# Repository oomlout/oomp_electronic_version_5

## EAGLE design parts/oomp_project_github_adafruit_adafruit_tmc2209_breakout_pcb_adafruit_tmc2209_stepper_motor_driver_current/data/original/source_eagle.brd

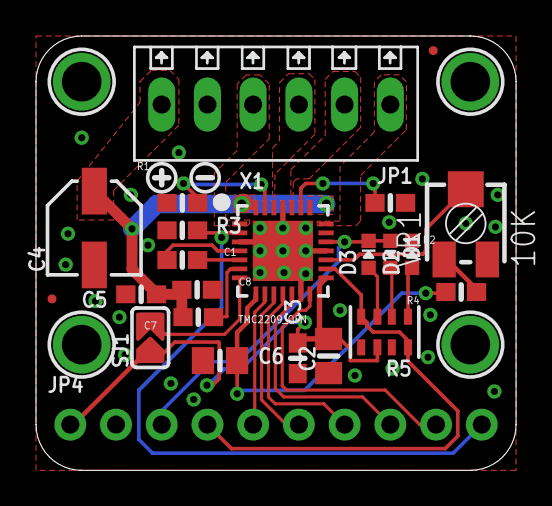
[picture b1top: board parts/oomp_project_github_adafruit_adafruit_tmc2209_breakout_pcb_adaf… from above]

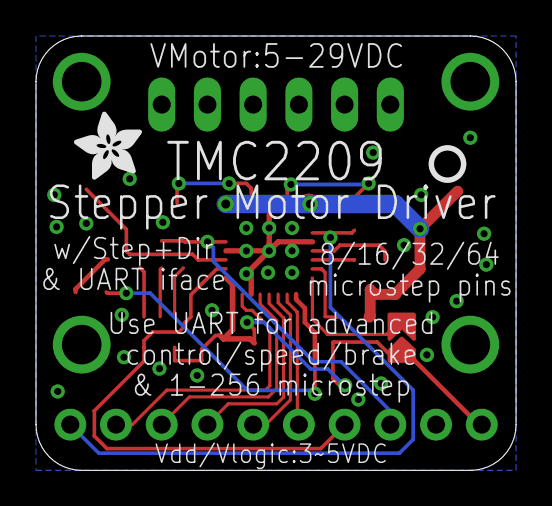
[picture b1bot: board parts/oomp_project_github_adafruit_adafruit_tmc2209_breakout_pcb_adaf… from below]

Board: 2 copper layers, 26.7 x 24.1 mm, 52 parts (2 on the bottom side), 27 nets.

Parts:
C1: 22nF/50V; 0603-NO
C2, C6: 10uF; 0805-NO
C3, C5, C7, C8: 0.22uF/50V; 0603-NO
C4: 22uF/50V; PANASONIC_C
D1: RED; CHIPLED_0603_NOOUTLINE
D2: YELLOW; CHIPLED_0603_NOOUTLINE
D3: GREEN; CHIPLED_0603_NOOUTLINE
JP1: 6-pin 2.54 Terminal; 1X06_2.54MMTERMINAL
JP4: 1X10_ROUND70
PLABEL0: PLABEL0
PLABEL1: PLABEL1
PLABEL2: PLABEL2
PLABEL3: PLABEL3
PLABEL4: PLABEL4
PLABEL5: PLABEL5
PLABEL6: PLABEL6
PLABEL7: PLABEL7
PLABEL8: PLABEL8
PLABEL9: PLABEL9
PLABEL10: PLABEL10
PLABEL11: PLABEL11
PLABEL12: PLABEL12
PLABEL13: PLABEL13
PLABEL14: PLABEL14
PLABEL15: PLABEL15
PLABEL16: PLABEL16
PLABEL17: PLABEL17
PLABEL18: PLABEL18
PLABEL19: PLABEL19
PLABEL20: PLABEL20
R1, R2: 0.05Ω/0.25W; 0603-NO
R3: 20K; 0603-NO
R4: 33K; 0603-NO
R5: 20K Pack; RESPACK_4X0603
SJ1: SOLDERJUMPER_ARROW_NOPASTE
U$7: SYMBOL_PLUS
U$8: SYMBOL_MINUS
U$10, U$11: FIDUCIAL_0.5MM
U$12: PCBFEAT-REV-040
U$18, U$22, U$26, U$27: MOUNTINGHOLE2.0; MOUNTINGHOLE_2.0_PLATED
U$24: ADAFRUIT_3.5MM
VR1: 10K; RTRIM3314J
X1: TMC2209_QFN; QFN28_5MM_MICROCHIP

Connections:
+5V: C6.2, R4.2, X1.8
BRA: R2.2, X1.23
BRB: R1.2, X1.27
DIAG: JP4.7, X1.11
DIR: D1.A, D3.C, JP4.3, X1.19
ENABLE: JP4.10, R3.2, X1.2
GND: C2.1, C3.1, C4.-, C5.2, C6.1, C8.2, D2.C, JP1.5, JP4.2, R1.1, R2.1, R3.1, R5.5, R5.7, VR1.1, X1.3, X1.13, X1.18, X1.25, X1.THERMAL
INDEX: JP4.8, X1.12
MS1: JP4.5, X1.9
MS2: JP4.6, X1.10
unnamed: D2.A, R5.1
unnamed: C1.1, X1.4
unnamed: C1.2, X1.5
unnamed: R4.1, VR1.3
unnamed: C7.1, X1.6
unnamed: D1.C, R5.2
unnamed: D3.A, R5.3
OUT1A: JP1.2, X1.24
OUT1B: JP1.1, X1.21
OUT2A: JP1.3, X1.26
OUT2B: JP1.4, X1.1
SPREAD: SJ1.2, X1.7
STEP: JP4.4, R5.4, R5.8, X1.16
UART: JP4.9, X1.14
VDD: C2.2, C3.2, JP4.1, R5.6, SJ1.1, X1.15
VMOTOR: C4.+, C5.1, C7.2, C8.1, JP1.6, X1.22, X1.28
VREF: VR1.2, X1.17

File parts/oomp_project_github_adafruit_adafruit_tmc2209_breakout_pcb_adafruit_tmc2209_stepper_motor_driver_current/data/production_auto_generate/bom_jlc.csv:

Comment,Designator,Footprint,LCSC Part #
,JP4,Adafruit TMC2209 Stepper Motor Driver-import-fps:1X10_ROUND70,C57369
,U$24,Adafruit TMC2209 Stepper Motor Driver-import-fps:ADAFRUIT_3.5MM,
,U$12,Adafruit TMC2209 Stepper Motor Driver-import-fps:PCBFEAT-REV-040,
,PLABEL0,Adafruit TMC2209 Stepper Motor Driver-import-fps:PLABEL0,
,PLABEL1,Adafruit TMC2209 Stepper Motor Driver-import-fps:PLABEL1,
,PLABEL10,Adafruit TMC2209 Stepper Motor Driver-import-fps:PLABEL10,
,PLABEL11,Adafruit TMC2209 Stepper Motor Driver-import-fps:PLABEL11,
,PLABEL12,Adafruit TMC2209 Stepper Motor Driver-import-fps:PLABEL12,
,PLABEL13,Adafruit TMC2209 Stepper Motor Driver-import-fps:PLABEL13,
,PLABEL14,Adafruit TMC2209 Stepper Motor Driver-import-fps:PLABEL14,
,PLABEL15,Adafruit TMC2209 Stepper Motor Driver-import-fps:PLABEL15,
,PLABEL16,Adafruit TMC2209 Stepper Motor Driver-import-fps:PLABEL16,
,PLABEL17,Adafruit TMC2209 Stepper Motor Driver-import-fps:PLABEL17,
,PLABEL18,Adafruit TMC2209 Stepper Motor Driver-import-fps:PLABEL18,
,PLABEL19,Adafruit TMC2209 Stepper Motor Driver-import-fps:PLABEL19,
,PLABEL2,Adafruit TMC2209 Stepper Motor Driver-import-fps:PLABEL2,
,PLABEL20,Adafruit TMC2209 Stepper Motor Driver-import-fps:PLABEL20,
,PLABEL3,Adafruit TMC2209 Stepper Motor Driver-import-fps:PLABEL3,
,PLABEL4,Adafruit TMC2209 Stepper Motor Driver-import-fps:PLABEL4,
,PLABEL5,Adafruit TMC2209 Stepper Motor Driver-import-fps:PLABEL5,
,PLABEL6,Adafruit TMC2209 Stepper Motor Driver-import-fps:PLABEL6,
,PLABEL7,Adafruit TMC2209 Stepper Motor Driver-import-fps:PLABEL7,
,PLABEL8,Adafruit TMC2209 Stepper Motor Driver-import-fps:PLABEL8,
,PLABEL9,Adafruit TMC2209 Stepper Motor Driver-import-fps:PLABEL9,
,U$8,Adafruit TMC2209 Stepper Motor Driver-import-fps:SYMBOL_MINUS,
,U$7,Adafruit TMC2209 Stepper Motor Driver-import-fps:SYMBOL_PLUS,
0.05Ω/0.25W,"R1,R2",Adafruit TMC2209 Stepper Motor Driver-import-fps:0603-NO,
0.22uF/50V,"C3,C5,C7,C8",Adafruit TMC2209 Stepper Motor Driver-import-fps:0603-NO,
10K,VR1,Adafruit TMC2209 Stepper Motor Driver-import-fps:RTRIM3314J,
10uF,"C2,C6",Adafruit TMC2209 Stepper Motor Driver-import-fps:0805-NO,
20K,R3,Adafruit TMC2209 Stepper Motor Driver-import-fps:0603-NO,
20K Pack,R5,Adafruit TMC2209 Stepper Motor Driver-import-fps:RESPACK_4X0603,
22nF/50V,C1,Adafruit TMC2209 Stepper Motor Driver-import-fps:0603-NO,
22uF/50V,C4,Adafruit TMC2209 Stepper Motor Driver-import-fps:PANASONIC_C,
33K,R4,Adafruit TMC2209 Stepper Motor Driver-import-fps:0603-NO,C4216
6-pin 2.54 Terminal,JP1,Adafruit TMC2209 Stepper Motor Driver-import-fps:1X06_2.54MMTERMINAL,C37208
FIDUCIAL_0.5MM,"U$10,U$11",Adafruit TMC2209 Stepper Motor Driver-import-fps:FIDUCIAL_0.5MM,
GREEN,D3,Adafruit TMC2209 Stepper Motor Driver-import-fps:CHIPLED_0603_NOOUTLINE,
RED,D1,Adafruit TMC2209 Stepper Motor Driver-import-fps:CHIPLED_0603_NOOUTLINE,
TMC2209_QFN,X1,Adafruit TMC2209 Stepper Motor Driver-import-fps:QFN28_5MM_MICROCHIP,
YELLOW,D2,Adafruit TMC2209 Stepper Motor Driver-import-fps:CHIPLED_0603_NOOUTLINE,

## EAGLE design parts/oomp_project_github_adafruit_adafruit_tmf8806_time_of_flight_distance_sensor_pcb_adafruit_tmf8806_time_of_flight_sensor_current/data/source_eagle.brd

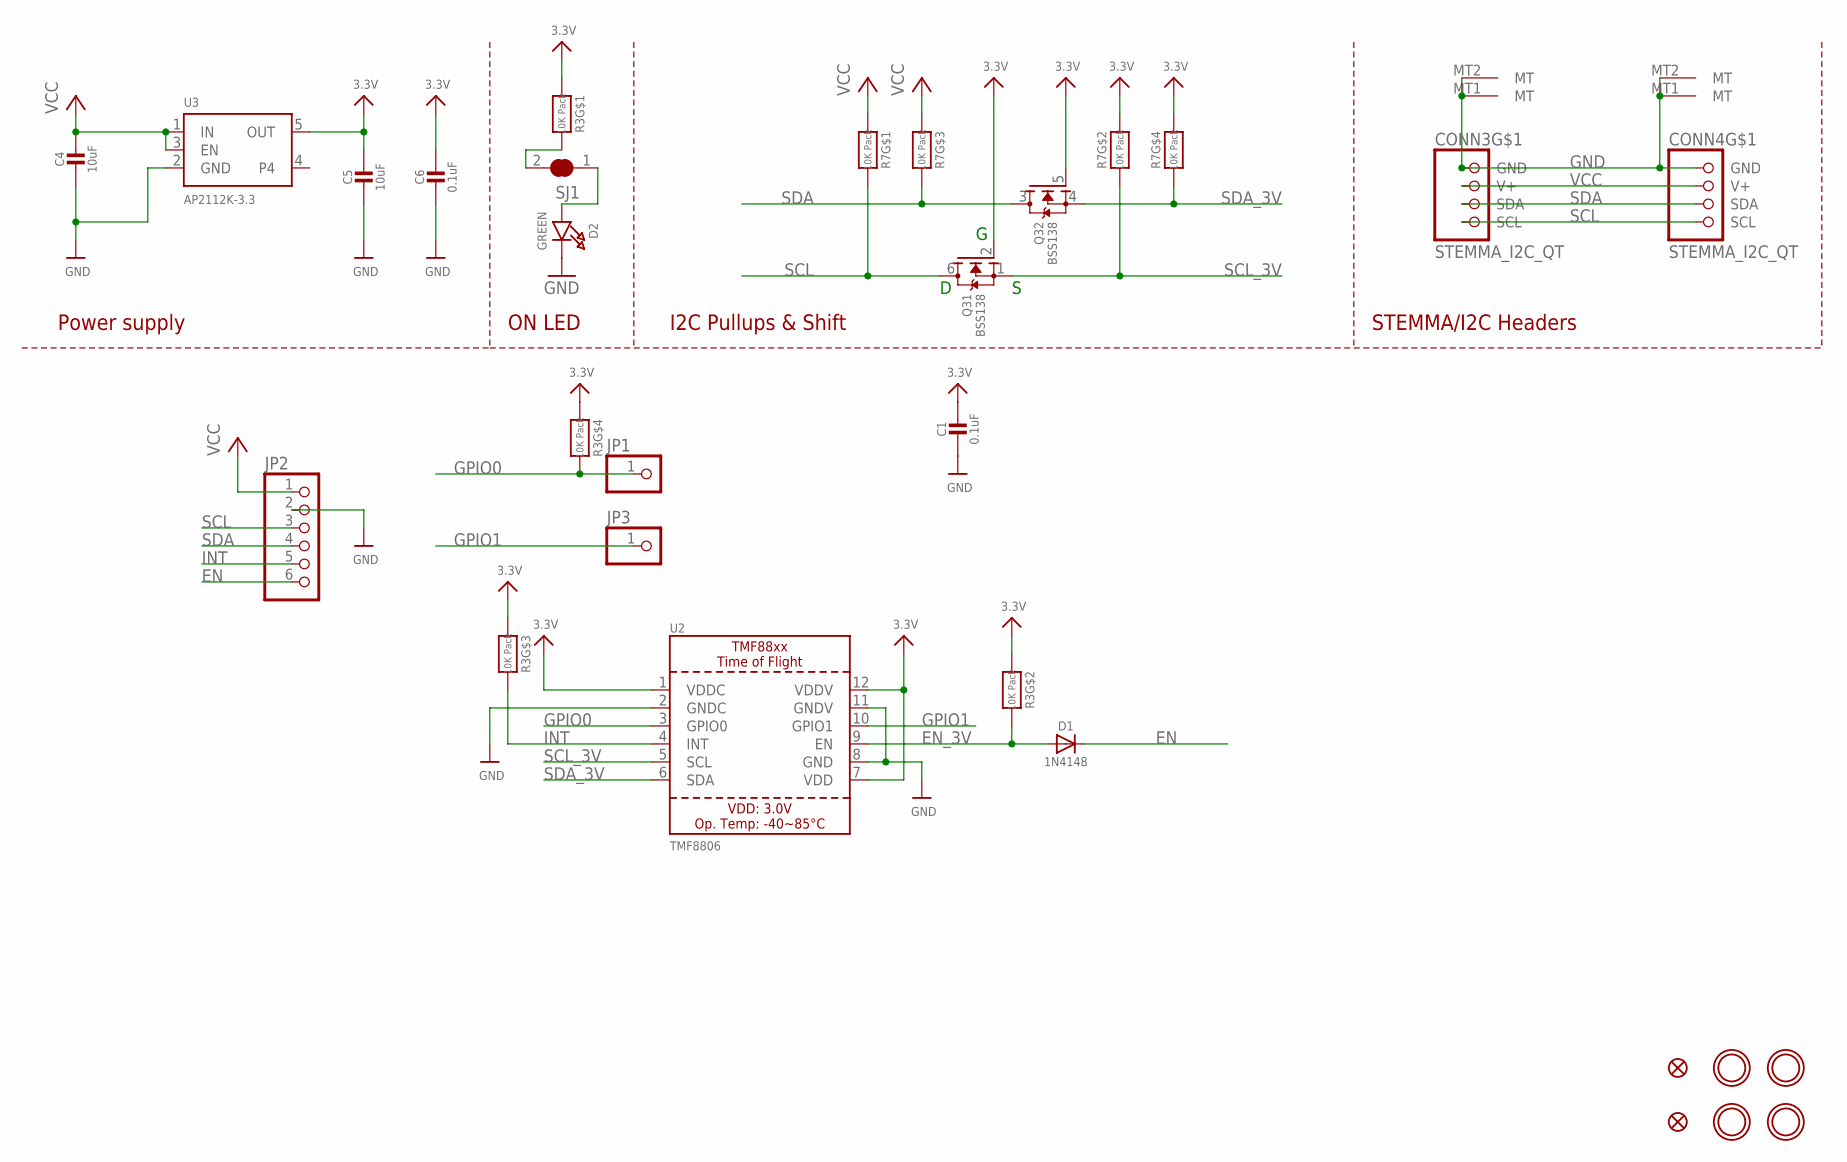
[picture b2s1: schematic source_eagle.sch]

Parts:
C1, C6: 0.1uF; 0603-NO
C4, C5: 10uF; 0805-NO
CONN3, CONN4: STEMMA_I2C_QT; JST_SH4
D1: 1N4148; SOD-323
D2: GREEN; CHIPLED_0603_NOOUTLINE
FID1, FID4: FIDUCIAL_0.5MM
JP1, JP3: HEADER-1X1ROUND; 1X01_ROUND
JP2: HEADER-1X670MIL; 1X06_ROUND_70
Q3: BSS138; SOT363
R3, R7: 10K Pack; RESPACK_4X0603
SJ1: SOLDERJUMPER_CLOSED; SOLDERJUMPER_CLOSEDWIRE
U2: TMF8806; TMF880X
U3: AP2112K-3.3; SOT23-5; JLC_ROTATION 0
U$30, U$31, U$33, U$34: MOUNTINGHOLE2.5; MOUNTINGHOLE_2.5_PLATED

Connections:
3.3V: C1.1, C5.1, C6.1, Q3.2 (G), Q3.5 (G), R3.1, R3.2 (1), R3.3 (1), R3.4 (1), R7.2 (1), R7.4 (1), U2.1 (VDDC), U2.7 (VDD), U2.12 (VDDV), U3.5 (OUT)
EN: D1.C, JP2.6
EN_3V: D1.A, R3.7 (2), U2.9 (EN)
GND: C1.2, C4.2, C5.2, C6.2, CONN3.1 (GND), CONN3.MT1 (MT), CONN3.MT2 (MT), CONN4.1 (GND), CONN4.MT1 (MT), CONN4.MT2 (MT), D2.C, JP2.2, U2.2 (GNDC), U2.8 (GND), U2.11 (GNDV), U3.2 (GND)
GPIO0: JP1.1, R3.5 (2), U2.3 (GPIO0)
GPIO1: JP3.1, U2.10 (GPIO1)
INT: JP2.5, R3.6 (2), U2.4 (INT)
unnamed: R3.8 (2), SJ1.2
unnamed: D2.A, SJ1.1
SCL: CONN3.4 (SCL), CONN4.4 (SCL), JP2.3, Q3.6 (D), R7.8 (2)
SCL_3V: Q3.1 (S), R7.7 (2), U2.5 (SCL)
SDA: CONN3.3 (SDA), CONN4.3 (SDA), JP2.4, Q3.3 (D), R7.6 (2)
SDA_3V: Q3.4 (S), R7.5 (2), U2.6 (SDA)
VCC: C4.1, CONN3.2 (V+), CONN4.2 (V+), JP2.1, R7.1, R7.3 (1), U3.1 (IN), U3.3 (EN)

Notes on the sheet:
I2C Pullups & Shift
STEMMA/I2C Headers
ON LED
Power supply

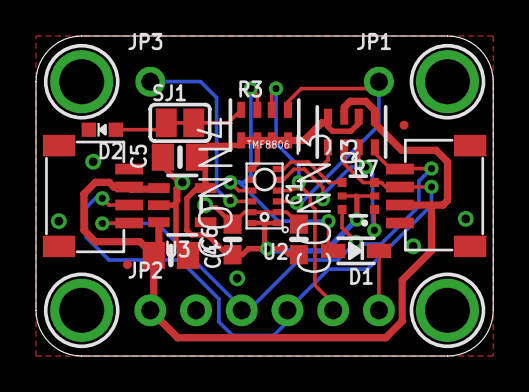
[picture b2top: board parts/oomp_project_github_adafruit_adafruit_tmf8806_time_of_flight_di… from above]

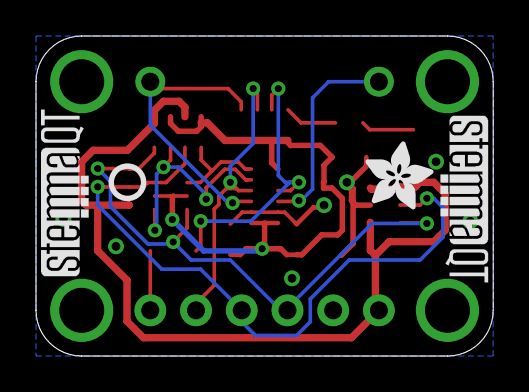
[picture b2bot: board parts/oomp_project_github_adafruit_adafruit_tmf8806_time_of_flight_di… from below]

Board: 2 copper layers, 25.4 x 17.8 mm, 42 parts (8 on the bottom side), 14 nets.

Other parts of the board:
PLABEL0: PLABEL0
PLABEL1: PLABEL1
PLABEL2: PLABEL2
PLABEL3: PLABEL3
PLABEL4: PLABEL4
PLABEL5: PLABEL5
PLABEL6: PLABEL6
PLABEL7: PLABEL7
PLABEL8: PLABEL8
PLABEL9: PLABEL9
PLABEL10: PLABEL10
PLABEL11: PLABEL11
PLABEL12: PLABEL12
PLABEL13: PLABEL13
PLABEL14: PLABEL14
U$36: ADAFRUIT_3.5MM
U$37: PCBFEAT-REV-040
U$38, U$39: STEMMAQT

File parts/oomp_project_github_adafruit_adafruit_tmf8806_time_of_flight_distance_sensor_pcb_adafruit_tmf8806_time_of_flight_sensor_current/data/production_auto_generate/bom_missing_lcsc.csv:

Designator,Comment,Footprint,OOMP ID,Reason
C4,10uF,Adafruit TMF8806 Time of Flight Sensor rev B-import-fps:0805-NO,electronic_capacitor_0805_10_micro_farad,No verified LCSC part number
C5,10uF,Adafruit TMF8806 Time of Flight Sensor rev B-import-fps:0805-NO,electronic_capacitor_0805_10_micro_farad,No verified LCSC part number
D1,1N4148,Adafruit TMF8806 Time of Flight Sensor rev B-import-fps:SOD-323,electronic_diode_switching_sod_323_onsemi_1n4148ws,No verified LCSC part number
D2,GREEN,Adafruit TMF8806 Time of Flight Sensor rev B-import-fps:CHIPLED_0603_NOOUTLINE,electronic_led_0603_green,No verified LCSC part number
PLABEL0,,Adafruit TMF8806 Time of Flight Sensor rev B-import-fps:PLABEL0,,No verified LCSC part number
PLABEL1,,Adafruit TMF8806 Time of Flight Sensor rev B-import-fps:PLABEL1,,No verified LCSC part number
PLABEL2,,Adafruit TMF8806 Time of Flight Sensor rev B-import-fps:PLABEL2,,No verified LCSC part number
PLABEL3,,Adafruit TMF8806 Time of Flight Sensor rev B-import-fps:PLABEL3,,No verified LCSC part number
PLABEL4,,Adafruit TMF8806 Time of Flight Sensor rev B-import-fps:PLABEL4,,No verified LCSC part number
PLABEL5,,Adafruit TMF8806 Time of Flight Sensor rev B-import-fps:PLABEL5,,No verified LCSC part number
PLABEL6,,Adafruit TMF8806 Time of Flight Sensor rev B-import-fps:PLABEL6,,No verified LCSC part number
PLABEL7,,Adafruit TMF8806 Time of Flight Sensor rev B-import-fps:PLABEL7,,No verified LCSC part number
PLABEL8,,Adafruit TMF8806 Time of Flight Sensor rev B-import-fps:PLABEL8,,No verified LCSC part number
PLABEL9,,Adafruit TMF8806 Time of Flight Sensor rev B-import-fps:PLABEL9,,No verified LCSC part number
PLABEL10,,Adafruit TMF8806 Time of Flight Sensor rev B-import-fps:PLABEL10,,No verified LCSC part number
PLABEL11,,Adafruit TMF8806 Time of Flight Sensor rev B-import-fps:PLABEL11,,No verified LCSC part number
PLABEL12,,Adafruit TMF8806 Time of Flight Sensor rev B-import-fps:PLABEL12,,No verified LCSC part number
PLABEL13,,Adafruit TMF8806 Time of Flight Sensor rev B-import-fps:PLABEL13,,No verified LCSC part number
PLABEL14,,Adafruit TMF8806 Time of Flight Sensor rev B-import-fps:PLABEL14,,No verified LCSC part number
Q3,BSS138,Adafruit TMF8806 Time of Flight Sensor rev B-import-fps:SOT363,electronic_transistor_sot_363_6_mosfet_n_channel_dual,No verified LCSC part number
U2,TMF8806,Adafruit TMF8806 Time of Flight Sensor rev B-import-fps:TMF880X,,No verified LCSC part number
U3,AP2112K-3.3,Adafruit TMF8806 Time of Flight Sensor rev B-import-fps:SOT23-5,electronic_ic_sot_23_5_power_management_linear_voltage_regulator_diodes_ap2112k_3_3,No verified LCSC part number
U$36,,Adafruit TMF8806 Time of Flight Sensor rev B-import-fps:ADAFRUIT_3.5MM,,No verified LCSC part number
U$37,,Adafruit TMF8806 Time of Flight Sensor rev B-import-fps:PCBFEAT-REV-040,,No verified LCSC part number
U$38,,Adafruit TMF8806 Time of Flight Sensor rev B-import-fps:STEMMAQT,,No verified LCSC part number
U$39,,Adafruit TMF8806 Time of Flight Sensor rev B-import-fps:STEMMAQT,,No verified LCSC part number

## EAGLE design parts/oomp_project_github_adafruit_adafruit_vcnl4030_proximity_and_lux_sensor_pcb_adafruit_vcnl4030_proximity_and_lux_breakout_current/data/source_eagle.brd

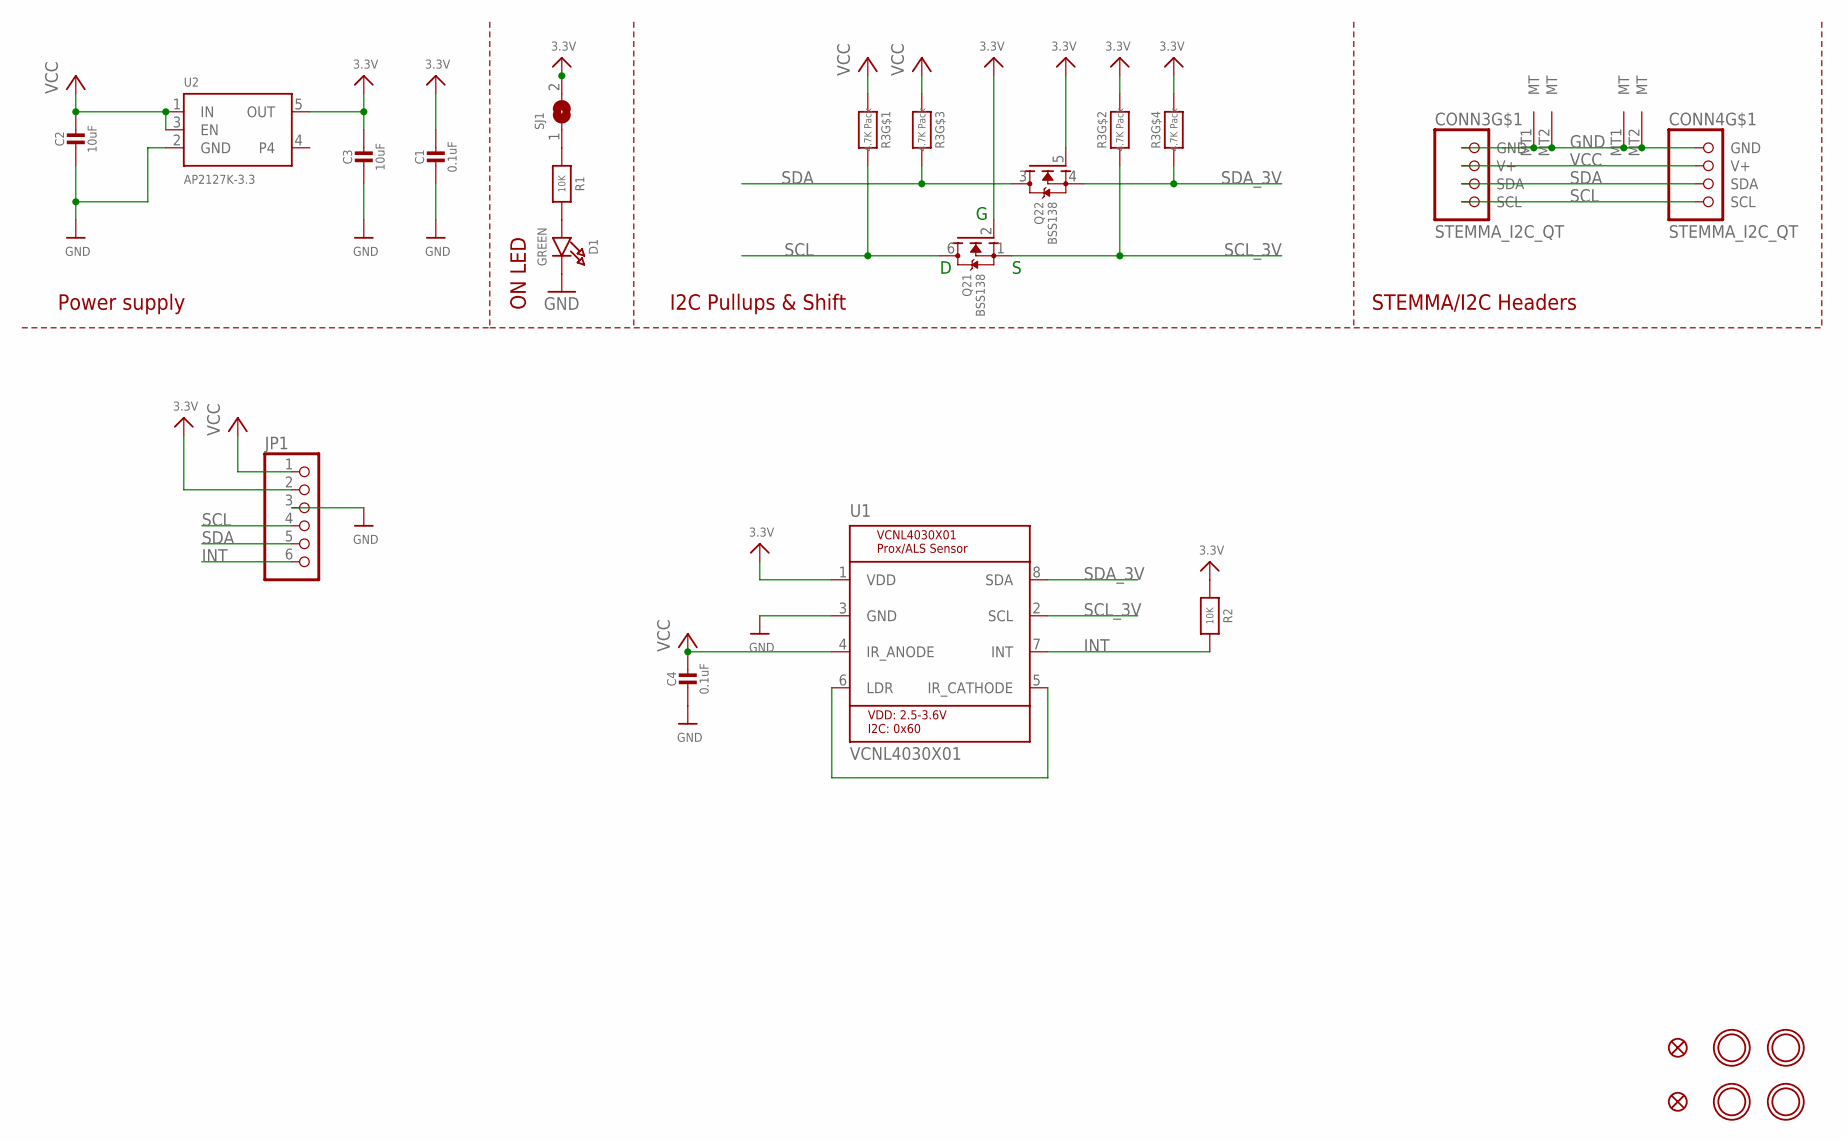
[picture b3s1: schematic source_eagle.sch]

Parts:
C1, C4: 0.1uF; 0603-NO
C2, C3: 10uF; 0805-NO
CONN3, CONN4: STEMMA_I2C_QT; JST_SH4
D1: GREEN; CHIPLED_0603_NOOUTLINE
FID3, FID4: FIDUCIAL_0.5MM
JP1: HEADER-1X670MIL; 1X06_ROUND_70
Q2: BSS138; SOT363
R1, R2: 10K; 0603-NO
R3: 4.7K Pack; RESPACK_4X0603
SJ1: SOLDERJUMPERCLOSED; SOLDERJUMPER_CLOSEDWIRE
U1: VCNL4030X01; VISHAY_VCNL4030X01
U2: AP2127K-3.3; SOT23-5
U$1, U$17, U$19, U$21: MOUNTINGHOLE2.5; MOUNTINGHOLE_2.5_PLATED

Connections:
3.3V: C1.1, C3.1, JP1.2, Q2.2 (G), Q2.5 (G), R2.1, R3.2 (1), R3.4 (1), SJ1.2, U1.1 (VDD), U2.5 (OUT)
GND: C1.2, C2.2, C3.2, C4.2, CONN3.1 (GND), CONN3.MT1 (MT), CONN3.MT2 (MT), CONN4.1 (GND), CONN4.MT1 (MT), CONN4.MT2 (MT), D1.C, JP1.3, U1.3 (GND), U2.2 (GND)
INT: JP1.6, R2.2, U1.7 (INT)
unnamed: D1.A, R1.2
unnamed: R1.1, SJ1.1
unnamed: U1.5 (IR_CATHODE), U1.6 (LDR)
SCL: CONN3.4 (SCL), CONN4.4 (SCL), JP1.4, Q2.6 (D), R3.8 (2)
SCL_3V: Q2.1 (S), R3.7 (2), U1.2 (SCL)
SDA: CONN3.3 (SDA), CONN4.3 (SDA), JP1.5, Q2.3 (D), R3.6 (2)
SDA_3V: Q2.4 (S), R3.5 (2), U1.8 (SDA)
VCC: C2.1, C4.1, CONN3.2 (V+), CONN4.2 (V+), JP1.1, R3.1, R3.3 (1), U1.4 (IR_ANODE), U2.1 (IN), U2.3 (EN)

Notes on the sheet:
I2C Pullups & Shift
STEMMA/I2C Headers
ON LED
Power supply

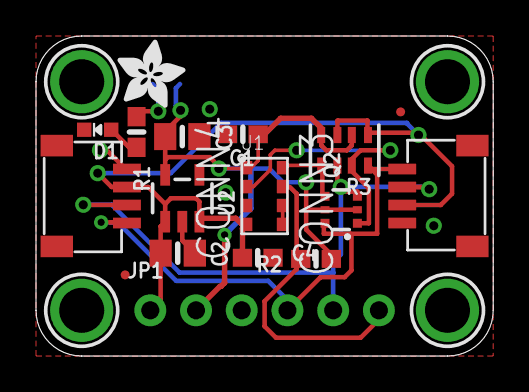
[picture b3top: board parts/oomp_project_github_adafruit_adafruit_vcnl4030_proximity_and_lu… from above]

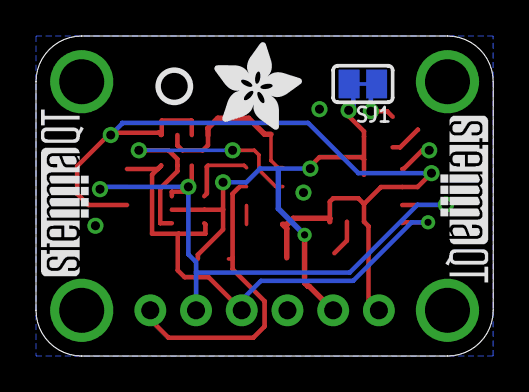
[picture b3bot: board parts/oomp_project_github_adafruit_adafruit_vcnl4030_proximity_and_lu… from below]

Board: 2 copper layers, 25.4 x 17.8 mm, 40 parts (10 on the bottom side), 11 nets.

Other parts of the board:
PLABEL0: PLABEL0
PLABEL1: PLABEL1
PLABEL2: PLABEL2
PLABEL3: PLABEL3
PLABEL4: PLABEL4
PLABEL5: PLABEL5
PLABEL8: PLABEL8
PLABEL10: PLABEL10
PLABEL11: PLABEL11
PLABEL12: PLABEL12
PLABEL13: PLABEL13
PLABEL14: PLABEL14
PLABEL15: PLABEL15
PLABEL16: PLABEL16
U$9: ADAFRUIT_5MM
U$22: ADAFRUIT_3.5MM
U$25: PCBFEAT-REV-040
U$30, U$31: STEMMAQT

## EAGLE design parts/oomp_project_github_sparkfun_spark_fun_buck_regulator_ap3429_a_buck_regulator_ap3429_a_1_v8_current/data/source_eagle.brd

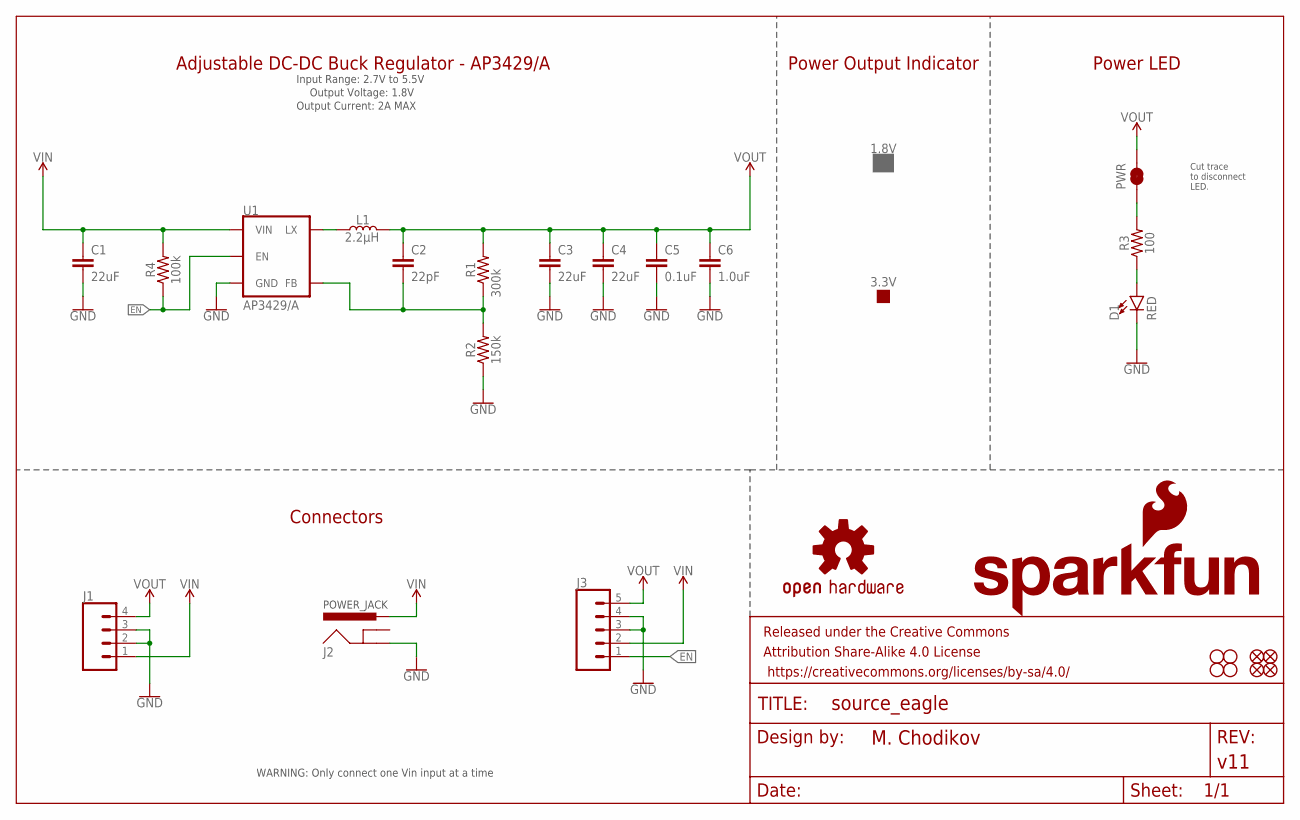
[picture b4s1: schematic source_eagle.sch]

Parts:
1.8V: PROD_ID_PASTE_NO-SILK; PRODUCT_IDENT_PASTE_NO-SILK
3.3V: PROD_ID_NO-PASTE_NO_SILK; PRODUCT_IDENT_NO_NO-SILK
C1, C3, C4: 22uF; 0805
C2: 22pF; 0402-TIGHT
C5: 0.1uF; 0603
C6: 1.0uF; 0603
D1: RED; LED-0603
FD1, FD2, FD3, FD4: FIDUCIALUFIDUCIAL; FIDUCIAL-MICRO
FRAME1: FRAME-LEDGER; CREATIVE_COMMONS
H1, H2, H3, H4: STAND-OFFTIGHT; STAND-OFF-TIGHT
J1: Screw Terminal; SCREWTERMINAL-3.5MM-4
J2: POWER_JACKPOWER_JACK_SLOT_COMBO; POWER_JACK_PTH_SLOT_BOTH
J3: Breakout Headers; 1X05_NO_SILK
L1: 2.2μH; INDUCTOR_4X4MM
LOGO1: OSHW-LOGOS; OSHW-LOGO-S
LOGO2: SFE_LOGO_NAME.1_INCH; SFE_LOGO_NAME_.1
LOGO3: SFE_LOGO_FLAME.1_INCH; SFE_LOGO_FLAME_.1
PWR: JUMPER-SMT_2_NC_TRACE_SILK; SMT-JUMPER_2_NC_TRACE_SILK
R1: 300k; 0603
R2: 150k; 0603
R3: 100; 0603
R4: 100k; 0603
U1: AP3429/A; SOT23-5

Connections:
EN: J3.1, R4.1, U1.1 (EN)
GND: C1.2, C3.2, C4.2, C5.2, C6.2, D1.C, J1.2, J1.3, J2.GND, J3.3, J3.4, R2.1, U1.2 (GND)
unnamed: L1.P$1 (1), U1.3 (LX)
unnamed: C2.2, R1.1, R2.2, U1.5 (FB)
unnamed: PWR.1, R3.2
unnamed: D1.A, R3.1
VIN: C1.1, J1.1, J2.PWR, J3.2, R4.2, U1.4 (VIN)
VOUT: C2.1, C3.1, C4.1, C5.1, C6.1, J1.4, J3.5, L1.P$2 (2), PWR.2, R1.2

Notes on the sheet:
Input Range: 2.7V to 5.5V
Adjustable DC-DC Buck Regulator - AP3429/A
Power LED
Connectors
POWER_JACK
Output Current: 2A MAX
WARNING: Only connect one Vin input at a time
Power Output Indicator
Cut trace to disconnect LED.
Output Voltage: 1.8V

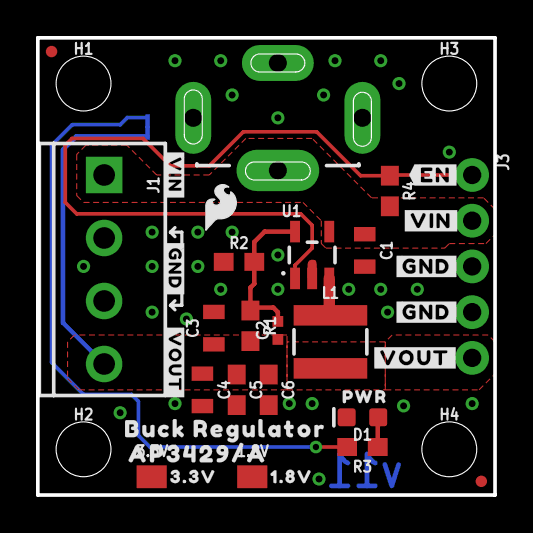
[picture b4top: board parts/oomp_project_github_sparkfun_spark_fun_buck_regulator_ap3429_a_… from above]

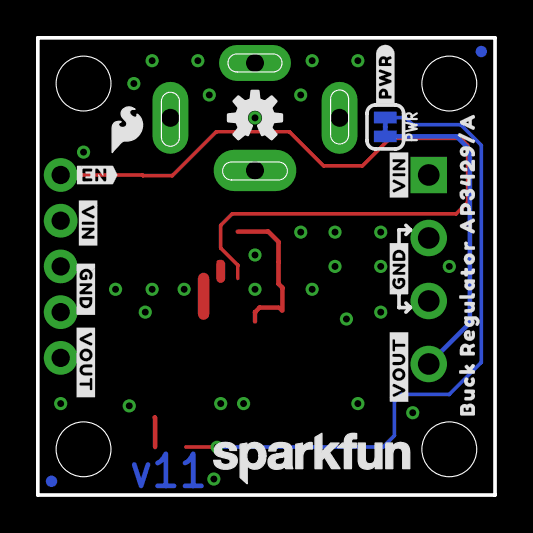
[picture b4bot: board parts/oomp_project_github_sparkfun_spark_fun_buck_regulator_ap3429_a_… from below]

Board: 2 copper layers, 25.4 x 25.4 mm, 55 parts (15 on the bottom side), 8 nets.

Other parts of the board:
U$1: SFE_LOGO_FLAME_.1
U$2: BUCK_REGULATOR24
U$3: AP3429#A25
U$4: #VOUT#3431
U$5, U$6: #GND#3432
U$7: #VIN#3433
U$8, U$10: #GND#3446
U$9, U$15: #VIN#3445
U$11, U$13: #VOUT#3447
U$12: #EN#3448
U$14: #PWR#3451
U$16: BUCK_REGULATOR_AP3429#A3453
U$17: ORDERING_INSTRUCTIONS
U$19: 1#8V3441
U$20: PWR3441
U$21: #VOUT#3437
U$22: #VIN#3438
U$23: 3#3V3441
U$24: #GND#3439
U$25: #EN#3443

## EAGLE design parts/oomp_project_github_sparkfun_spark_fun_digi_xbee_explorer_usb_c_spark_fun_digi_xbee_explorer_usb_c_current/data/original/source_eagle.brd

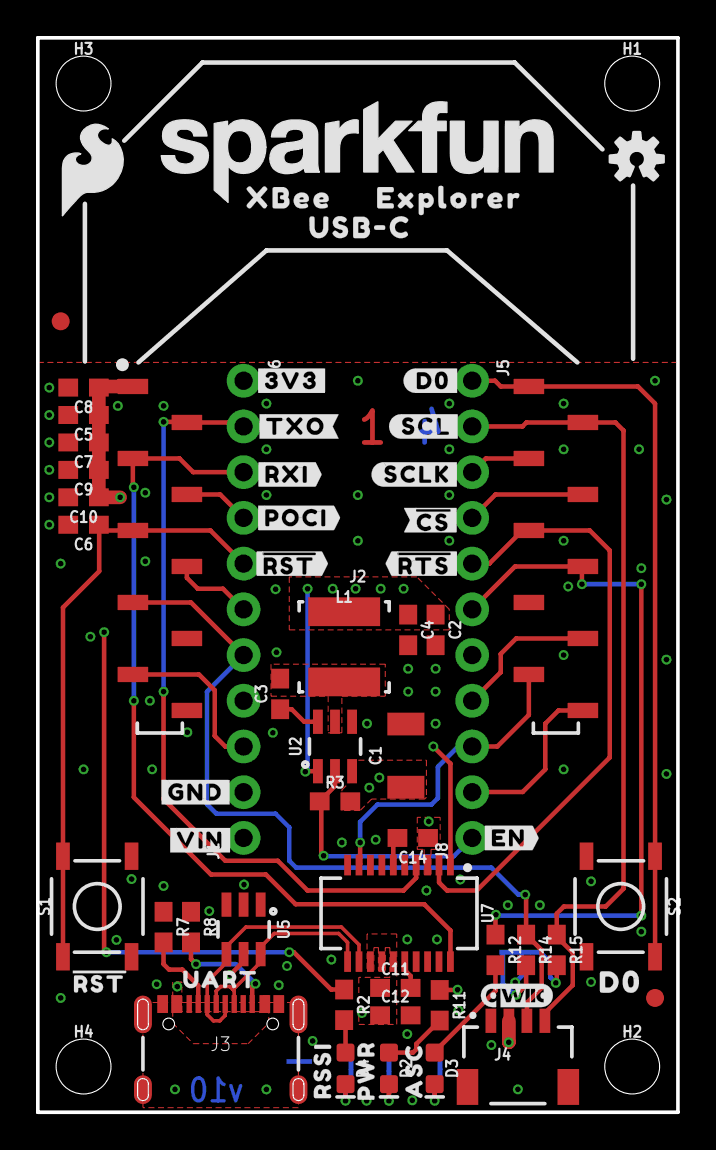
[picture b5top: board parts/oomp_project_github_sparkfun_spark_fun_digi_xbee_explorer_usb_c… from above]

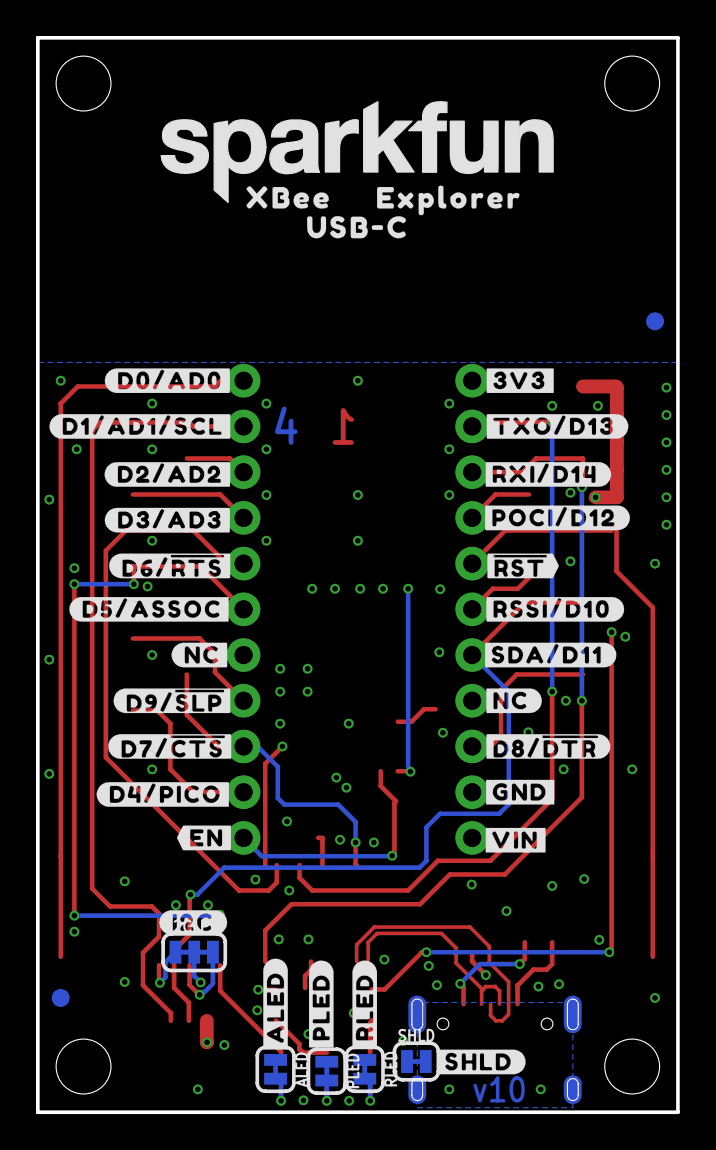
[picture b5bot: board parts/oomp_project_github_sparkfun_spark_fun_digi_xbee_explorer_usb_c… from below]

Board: 4 copper layers, 35.6 x 59.7 mm, 109 parts (38 on the bottom side), 35 nets.

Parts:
ALED: JUMPER-SMT_2_NC_TRACE_SILK; SMT-JUMPER_2_NC_TRACE_SILK
C1: 10uF; 1210
C2, C4: 22uF; 0603
C3, C9, C11, C14: 0.1uF; 0603
C5: 47pF; 0603
C6, C7: 10nF; 0603
C8: 10pF; 0603
C10: 10uF; 0603
C12: 4.7uF; 0603
D2: Red; LED-0603
D3: BLUE; LED-0603
D4: Yellow; LED-0603
FD1, FD2, FD3, FD4: FIDUCIAL1X2; FIDUCIAL-1X2
FRAME1: FRAME-LEDGER; CREATIVE_COMMONS
H1, H2, H3, H4: STAND-OFFTIGHT; STAND-OFF-TIGHT
I2C_PU: JUMPER-SMT_3_2-NC_TRACE_SILK; SMT-JUMPER_3_2-NC_TRACE_SILK
J1, J8: 1X01_NO_SILK_STAND
J2: XBEE3-SMD
J3: USB Female Type C Connector; USB-C-16P-4LAYER-ISOLATED
J4: QWIIC_RIGHT_ANGLE; JST04_1MM_RA
J5, J6: 1X10_NO_SILK
L1: 3.9UH; INDUCTOR_3.9UH
LOGO1: SFE_LOGO_NAME.2_INCH; SFE_LOGO_NAME_.2
LOGO2: OSHW-LOGOS; OSHW-LOGO-S
LOGO3: QWIIC_LOGO_4MM; QWIIC_4MM
LOGO4: SPECIAL_INSTRUCTIONS-ORDERING; ORDERING_INSTRUCTIONS
PLED: JUMPER-SMT_2_NC_TRACE_SILK; SMT-JUMPER_2_NC_TRACE_SILK
R2, R12, R14, R15: 2.2k; 0603
R3: 10k; 0603
R7, R8: 5.1k; 0603
R11: 4.7k; 0603
RLED: JUMPER-SMT_2_NC_TRACE_SILK; SMT-JUMPER_2_NC_TRACE_SILK
S1, S2: TACTILE_SWITCH_SMD_5.2MM
SHLD: JUMPER-SMT_2_NC_TRACE_SILK; SMT-JUMPER_2_NC_TRACE_SILK
U2: AP63203; SOT23-6
U5: ESD Diode; SOT-23-6
U7: FT231XS; SSOP20_L
U$1: RSSI31
U$2: PWR29
U$3, U$12: #GND#0
U$4: #SHLD#36
U$5: #NC#1
U$6: #D3#AD3#23
U$7: #NC#3
U$8: #D0#AD0#18
U$9, U$44: #3V3#1
U$10, U$23: XBEE340
U$11: #D1#AD1#SCL#8
U$13: #D8##DTR##27
U$14: #RSSI#D10#17
U$15: #SDA#D11#9
U$16: ##RST##15
U$17: #POCI#D12#24
U$18: #RXI#D14#15
U$19: #D2#AD2#19
U$20: #D6##RTS##25
U$21: #TXO#8
U$22: #TXO#D13#13
U$24, U$25: USB#C1342
U$26: #I2C#33
U$27: #RXI#7
U$28: UART34
U$29: ASC32
U$30: #RST#30
U$31, U$32: EXPLORER1344
U$35: #D5#ASSOC#25
U$36: #D9##SLP##28
U$37: #D7##CTS##26
U$38: #D4#PICO#25
U$40: D03
U$45: #POCI#32
U$46, U$66: #VIN#4
U$48: #EN#17
U$49: #ALED#21
U$51: #RLED#22
U$52: #PLED#20
U$54: ##RST##13
U$58: ##RTS##14
U$59: ##CS##26
U$60: #SCLK#33
U$61: SFE_LOGO_FLAME_.2
U$63: SFE_LOGO_NAME_.2
U$64: #SCL#9
U$65: #D0#3
U$67: #EN#15

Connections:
3.3V: C2.1, C4.1, C5.1, C7.1, C8.1, C9.1, C10.1, C11.1, C12.1, C14.1, I2C_PU.2, J2.1, J4.2, J6.1, L1.P$2, R11.1, U2.1, U7.3, U7.13, U7.14, U7.15
!RESET!: C6.1, J2.5, J6.5, S1.1, S1.2
D0: J2.20, J5.1, S2.1, S2.2
D1/SCL: J2.19, J4.4, J5.2, R15.1
D2/SPI_CLK: J2.18, J5.3
D3/SPI_!CS!: J2.17, J5.4
D4/SPI_PICO: J2.11, J5.10
D5/ASSOCIATE: J2.15, J5.6, R12.1
D6/!RTS!: J2.16, J5.5, U7.2
D7/!CTS!: J2.12, J5.9, U7.9
D8/!DTR!: J2.9, J6.9, U7.1
D9/!SLEEP!: J2.13, J5.8
D10/RSSI_PWM: J2.6, J6.6, R2.1
D11/SDA: J2.7, J4.3, J6.7, R14.1
D12/SPI_POCI: J2.4, J6.4
D13/TXO: J2.2, J6.2, U7.4
D14/RXI: J2.3, J6.3, U7.20
D+: J3.A6, J3.B6, U5.6, U7.11
D-: J3.A7, J3.B7, U5.4, U7.12
EN: J8.1, R3.1, U2.2
GND: ALED.1, C1.2, C2.2, C4.2, C5.2, C6.2, C7.2, C8.2, C9.2, C10.2, C11.2, C12.2, C14.2, J2.10, J3.GND, J3.GND2, J4.1, J6.10, PLED.1, R7.1, R8.1, RLED.1, S1.3, S1.4, S2.3, S2.4, SHLD.1, U2.4, U5.2, U7.6, U7.16
unnamed: C3.1, U2.6
unnamed: D4.A, R2.2
unnamed: D4.C, RLED.2
unnamed: J3.B5, R8.2
unnamed: J3.A5, R7.2
unnamed: D2.A, R11.2
unnamed: C3.2, L1.P$1, U2.5
unnamed: I2C_PU.3, R14.2
unnamed: D3.A, R12.2
unnamed: I2C_PU.1, R15.2
unnamed: ALED.2, D3.C
unnamed: D2.C, PLED.2
SHLD: J3.SHLD1, J3.SHLD2, J3.SHLD3, J3.SHLD4, J3.SHLD5, J3.SHLD6, J3.SHLD7, J3.SHLD8, SHLD.2
VIN: C1.1, J1.1, J3.VBUS1, J3.VBUS2, R3.2, U2.3, U5.5

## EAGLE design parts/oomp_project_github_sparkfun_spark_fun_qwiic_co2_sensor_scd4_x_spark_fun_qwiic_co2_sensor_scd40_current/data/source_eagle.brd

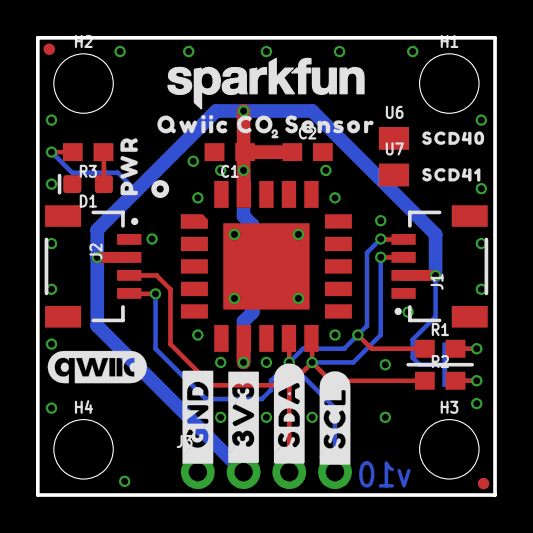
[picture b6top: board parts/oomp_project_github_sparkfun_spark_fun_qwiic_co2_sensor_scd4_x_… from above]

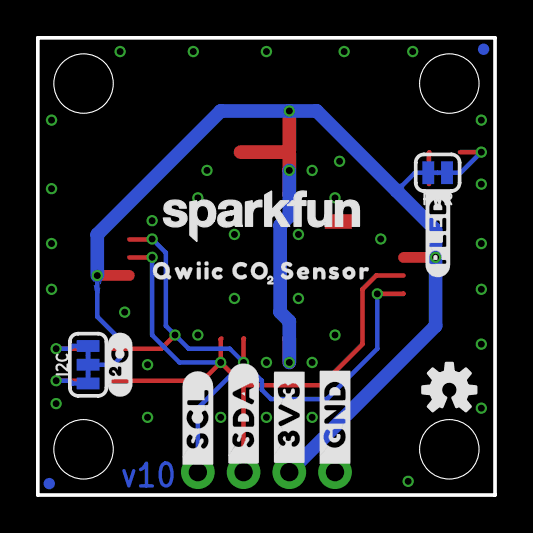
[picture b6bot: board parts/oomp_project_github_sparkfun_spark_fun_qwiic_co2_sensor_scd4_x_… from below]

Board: 2 copper layers, 25.4 x 25.4 mm, 49 parts (16 on the bottom side), 8 nets.

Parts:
C1: 0.1uF; 0603
C2: 4.7uF; 0603
D1: RED; LED-0603
FD1, FD2, FD3, FD4: FIDUCIALUFIDUCIAL; FIDUCIAL-MICRO
FRAME1: FRAME-LETTER; CREATIVE_COMMONS
H1, H2, H3, H4: STAND-OFF
I2C: I2C; SMT-JUMPER_3_2-NC_TRACE_SILK
J1, J2: QWIIC_RA; JST04_1MM_RA
J3: PTH; 1X04_NO_SILK
LOGO1: QWIIC_LOGO_CONNECTOR; QWIIC_5.5MM
LOGO2: OSHW-LOGOS; OSHW-LOGO-S
LOGO3: SFE_LOGO_NAME_FLAMEBLANK; BLANK
PWR: PWR; SMT-JUMPER_2_NC_TRACE_SILK
R1, R2: 2.2k; 0603
R3: 4.7k; 0603
U1: SCD40/1; SCD4X
U6: SCD40; PRODUCT_IDENT_PASTE_NO-SILK
U7: SCD41; PRODUCT_IDENT_NO_NO-SILK
U$1, U$18: #_GND#14
U$2, U$19: #_3V3#15
U$3, U$20: #_SDA#15
U$4, U$21: #_SCL#16
U$5, U$12: SFE_LOGO_NAME_.1
U$6: SCD414140404021
U$7: SCD40414140404022
U$8, U$13: QWIIC_CO0
U$9, U$14: SENSOR0
U$10, U$15: 20
U$11: SFE_LOGO_FLAME_STOP_.1
U$16: #PLED#21
U$17: #I�C#0
U$22: ORDERING_INSTRUCTIONS
U$23: PWR0

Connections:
3.3V: C1.1, C2.1, I2C.2, J1.2, J2.2, J3.2, PWR.2, U1.7, U1.19
GND: C1.2, C2.2, D1.C, J1.1, J2.1, J3.1, U1.6, U1.20, U1.CP
unnamed: I2C.1, R2.2
unnamed: I2C.3, R1.2
unnamed: PWR.1, R3.2
unnamed: D1.A, R3.1
SCL: J1.4, J2.4, J3.4, R1.1, U1.9
SDA: J1.3, J2.3, J3.3, R2.1, U1.10

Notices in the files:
parts and their libraries:
microbuilder: This work is placed in the public domain, and may be freely used for commercial and non-commercial work with the following conditions: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
SparkFun-Aesthetics: Licensing: Creative Commons ShareAlike 4.0 International - https://creativecommons.org/licenses/by-sa/4.0
